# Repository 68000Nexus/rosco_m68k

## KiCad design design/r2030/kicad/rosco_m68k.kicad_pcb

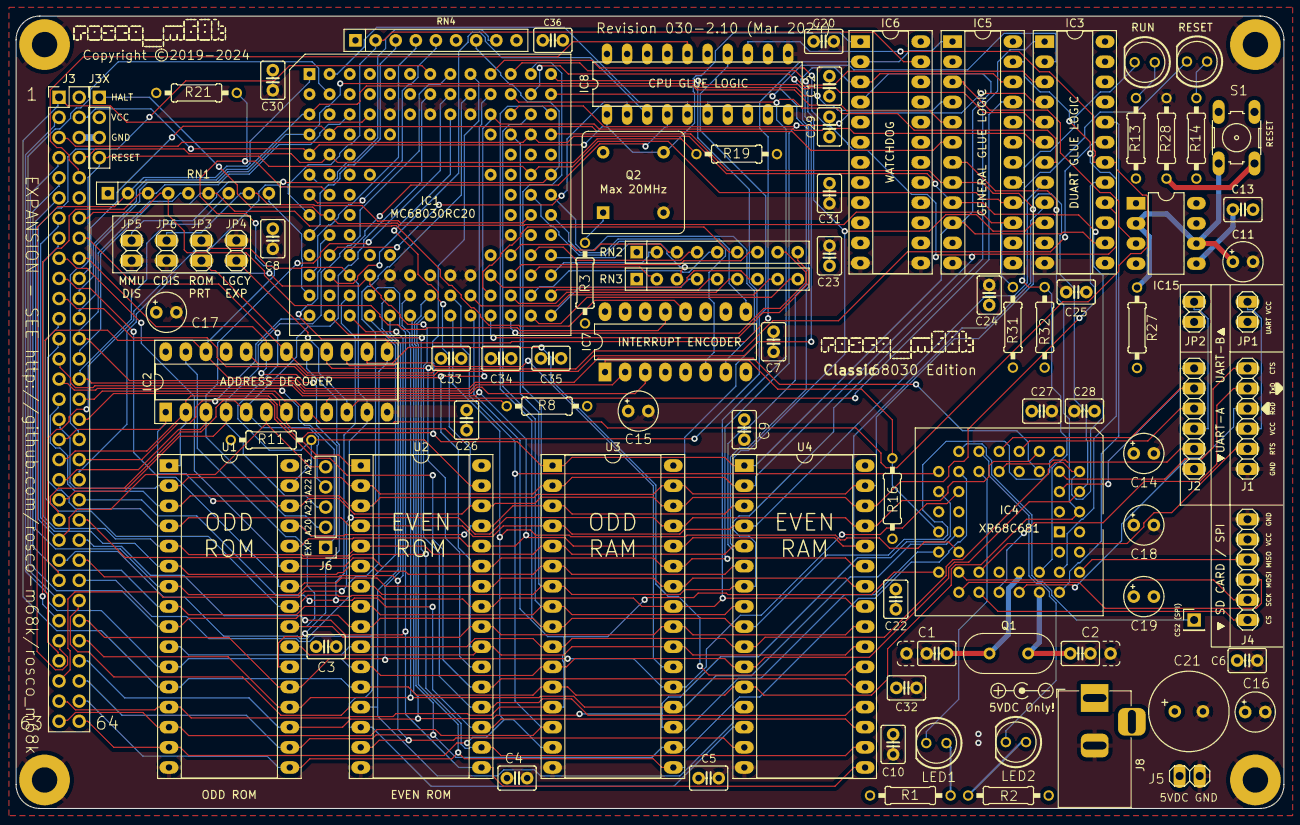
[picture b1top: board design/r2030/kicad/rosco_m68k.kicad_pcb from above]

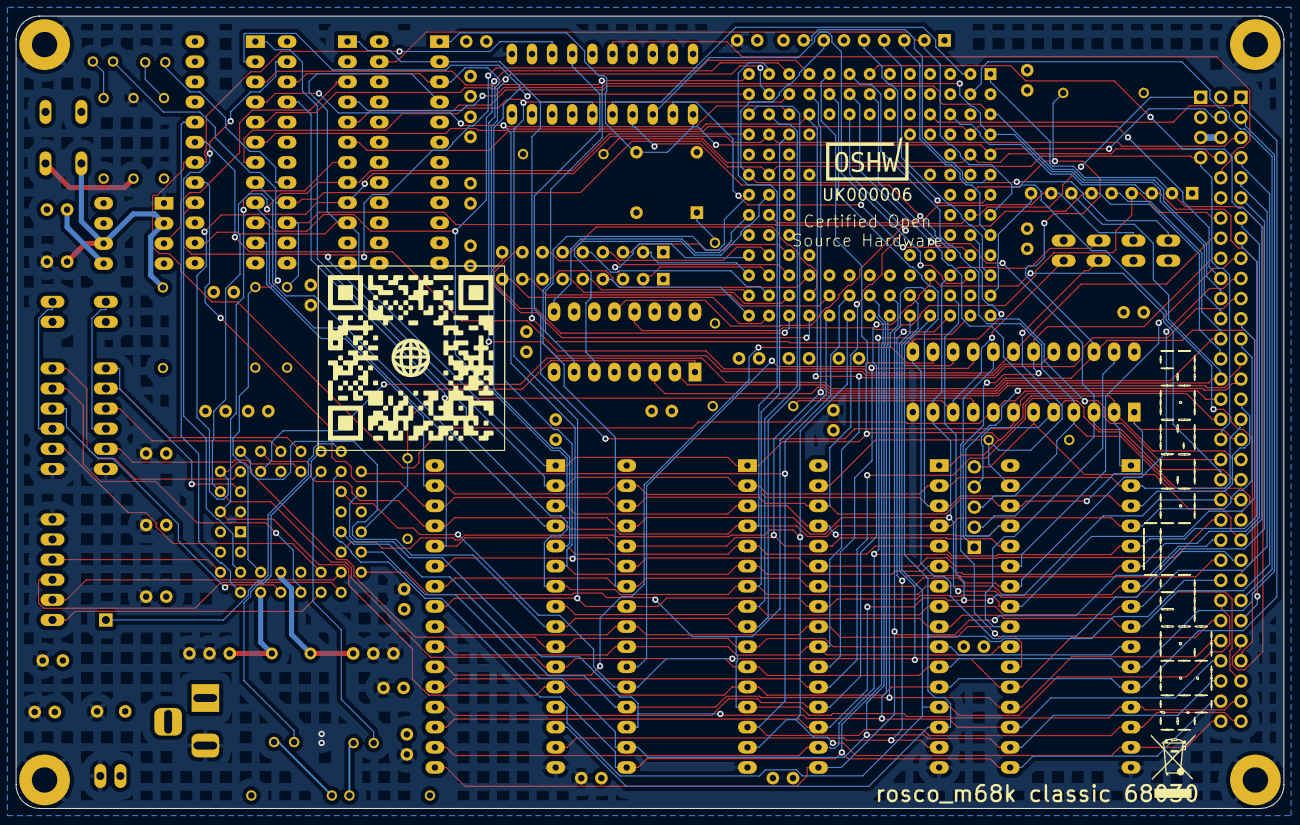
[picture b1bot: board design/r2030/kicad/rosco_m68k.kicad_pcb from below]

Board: 4 copper layers, 160.0 x 100.0 mm, 97 parts (2 on the bottom side), 135 nets.

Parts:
C1, C2: 7pF; C2.5_or_3.5-3
C3, C4, C5, C6, C7, C8, C9, C10, C12, C13, C20, C22, C23, C24, C25, C26, C27, C28, C29, C30, C31, C32, C33, C34, C35, C36: 100nF; C2.5-3
C11, C14, C15, C16, C17, C18, C19: 100uF; E2,5-5
C21: 470uF; E3,5-10
H1, H2, H3, H4: MountingHole; MountingHole_3.2mm_M3_Pad
IC1: MC68030RC_PGA; MC68030RC
IC2, IC3, IC5, IC6: ATF22V10C; DIP-24_W7.62mm_Socket_LongPads
IC4: XR68C681CJTR-F; PLCC-44_THT-Socket
IC7: 74LS148; DIP-16_W7.62mm_LongPads
IC8: ATF16V8BQL; DIL20
IC15: 555N; DIP-8_W7.62mm_LongPads
J1: UART_A; 1X06
J2: UART_B; 1X06
J3: Conn_02x32_Odd_Even; PinHeader_2x32_P2.54mm_Vertical
J3-X1: Conn_01x04_Male; PinHeader_1x04_P2.54mm_Vertical
J4: Conn_01x06; 1X06
J5: PWR; 1X02
J6: Conn_01x05_Male; PinHeader_1x05_P2.54mm_Vertical
J7: Conn_01x01_Male; PinHeader_1x01_P2.54mm_Vertical
J8: Jack-DC; BarrelJack_Horizontal
JP1, JP2, JP3, JP4, JP5, JP6: Jumper; 1X02
LED1, LED3: GREEN; LED5MM
LED2, LED4: RED; LED5MM
OSHW_Mono_0.25_Scale: UK000006; OSHW_Mono_0.25_Scale
Q1: 3.6864MHz; Crystal_HC49-4H_Vertical
Q2: 5H8ET-20.000; Oscillator_DIP-8
R1, R2, R13, R14: 330R; 0207_10
R3, R8, R16, R31, R32: 4K7; 0207_10
R11, R19: 10K; 0207_10
R21: 1K2; 0207_10
R27: 2K2; 0207_10
R28: 270R; 0207_10
RN1, RN4: 4K7; R_Array_SIP9
RN2: 10K; R_Array_SIP9
RN3: R_Network08; R_Array_SIP9
S1: 10-XX; B3F-10XX
U1, U2: SST39SF040; DIP-32_W15.24mm_Socket_LongPads
U3, U4: AS6C4008-55PCN; DIP-32_W15.24mm_Socket_LongPads
rosco_m68k, rosco_m68k_mid: SM-rosco_m68k_logo
weee: WEEE-Logo_5.6x8mm_SilkScreen

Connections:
A0: IC1.A2 (A0), IC8.5 (I4)
A1: IC1.C4 (A1), IC4.2 (A1), IC5.7 (I7), J3.1, U1.12 (A0), U2.12 (A0), U3.12 (A0), U4.12 (A0)
A2: IC1.D13 (A2), IC4.4 (A2), IC5.8 (I8), J3.3, U1.11 (A1), U2.11 (A1), U3.11 (A1), U4.11 (A1)
A3: IC1.D12 (A3), IC4.6 (A3), IC5.9 (I9), J3.5, U1.10 (A2), U2.10 (A2), U3.10 (A2), U4.10 (A2)
A4: IC1.C13 (A4), IC4.7 (A4), J3.7, U1.9 (A3), U2.9 (A3), U3.9 (A3), U4.9 (A3)
A5: IC1.C12 (A5), J3.9, U1.8 (A4), U2.8 (A4), U3.8 (A4), U4.8 (A4)
A6: IC1.D11 (A6), IC3.1 (I1/CLK), J3.11, U1.7 (A5), U2.7 (A5), U3.7 (A5), U4.7 (A5)
A7: IC1.B13 (A7), IC3.2 (I2), J3.13, U1.6 (A6), U2.6 (A6), U3.6 (A6), U4.6 (A6)
A8: IC1.B12 (A8), IC3.3 (I3), J3.15, U1.5 (A7), U2.5 (A7), U3.5 (A7), U4.5 (A7)
A9: IC1.C11 (A9), IC3.4 (I4/PD), J3.17, U1.27 (A8), U2.27 (A8), U3.27 (A8), U4.27 (A8)
A10: IC1.A13 (A10), IC3.5 (I5), J3.19, U1.26 (A9), U2.26 (A9), U3.26 (A9), U4.26 (A9)
A11: IC1.C10 (A11), IC3.6 (I6), J3.21, U1.23 (A10), U2.23 (A10), U3.23 (A10), U4.23 (A10)
A12: IC1.B11 (A12), IC3.7 (I7), J3.23, U1.25 (A11), U2.25 (A11), U3.25 (A11), U4.25 (A11)
A13: IC1.A12 (A13), IC3.8 (I8), J3.25, U1.4 (A12), U2.4 (A12), U3.4 (A12), U4.4 (A12)
A14: IC1.B10 (A14), IC3.9 (I9), J3.27, U1.28 (A13), U2.28 (A13), U3.28 (A13), U4.28 (A13)
A15: IC1.A11 (A15), IC3.10 (I10), J3.29, U1.29 (A14), U2.29 (A14), U3.3 (A14), U4.3 (A14)
A16: IC1.B9 (A16), IC3.11 (I11), J3.31, U1.3 (A15), U2.3 (A15), U3.31 (A15), U4.31 (A15)
A17: IC1.A10 (A17), IC3.16 (IO3), J3.33, U1.2 (A16), U2.2 (A16), U3.2 (A16), U4.2 (A16)
A18: IC1.C8 (A18), IC2.1 (I1/CLK), IC3.17 (I04), J3.35, U1.30 (A17), U2.30 (A17), U3.30 (A17), U4.30 (A17)
A19: IC1.A9 (A19), IC2.2 (I2), IC3.14 (IO1), IC5.10 (I10), IC6.4 (I4/PD), J3.37, U1.1 (A18), U2.1 (A18), U3.1 (A18), U4.1 (A18)
A20: IC1.B8 (A20), IC2.3 (I3), J3.39, J6.2
A21: IC1.A8 (A21), IC2.4 (I4/PD), J3.41, J6.3
A22: IC1.B7 (A22), IC2.5 (I5), J3.43, J6.4
A23: IC1.A7 (A23), IC2.6 (I6), J3.45, J6.5
AS: IC1.J2 (AS), IC2.13 (I13), IC5.1 (I1/CLK), IC6.2 (I2), IC8.6 (I5), J3.47
BERR: IC1.H1 (BERR), IC6.23 (IO10), J3.49, RN4.2 (R1)
BG: IC1.B2 (BG), J3.51
BGACK: IC1.C3 (BGACK), J3.53, RN1.3 (R2)
BOOT: IC2.9 (I9), IC5.21 (IO8)
BR: IC1.A1 (BR), J3.55, RN1.2 (R1)
CBACK: IC1.J1 (CBACK), RN4.3 (R2)
CDIS: IC1.H12 (CDIS), JP6.1 (A), RN1.8 (R7)
CIIN: IC1.L1 (CIIN), RN4.4 (R3)
CLK: IC1.E1 (CLKIN), IC6.1 (I1/CLK), IC8.1 (CLK), J3.4, Q2.5 (OUT)
CPUSP: IC2.20 (IO7), IC5.22 (IO9), IC6.3 (I3)
CTSA: IC4.8 (IP0), J1.6
CTSB: IC4.5 (IP1), J2.6
D0: IC1.N9 (D16), IC4.28 (D0), J3.61, U1.13 (D0), U3.13 (DQ0)
D1: IC1.M8 (D17), IC4.18 (D1), J3.63, U1.14 (D1), U3.14 (DQ1)
D2: IC1.N8 (D18), IC4.27 (D2), J3.64, U1.15 (D2), U3.15 (DQ2)
D3: IC1.N7 (D19), IC4.19 (D3), J3.62, U1.17 (D3), U3.17 (DQ3)
D4: IC1.M7 (D20), IC4.26 (D4), J3.60, U1.18 (D4), U3.18 (DQ4)
D5: IC1.N6 (D21), IC4.20 (D5), J3.58, U1.19 (D5), U3.19 (DQ5)
D6: IC1.M6 (D22), IC4.25 (D6), J3.56, U1.20 (D6), U3.20 (DQ6)
D7: IC1.N5 (D23), IC4.21 (D7), J3.54, U1.21 (D7), U3.21 (DQ7)
D8: IC1.M5 (D24), J3.52, U2.13 (D0), U4.13 (DQ0)
D9: IC1.N4 (D25), J3.50, U2.14 (D1), U4.14 (DQ1)
D10: IC1.N3 (D26), J3.48, U2.15 (D2), U4.15 (DQ2)
D11: IC1.M4 (D27), J3.46, U2.17 (D3), U4.17 (DQ3)
D12: IC1.N2 (D28), J3.44, U2.18 (D4), U4.18 (DQ4)
D13: IC1.M3 (D29), J3.42, U2.19 (D5), U4.19 (DQ5)
D14: IC1.L4 (D30), J3.40, U2.20 (D6), U4.20 (DQ6)
D15: IC1.N1 (D31), J3.38, U2.21 (D7), U4.21 (DQ7)
DBEN: IC1.M1 (DBEN), RN1.9 (R8)
DS: IC1.K2 (DS), IC8.2 (I1)
DSACK0: IC1.F1 (DSACK0), RN4.8 (R7)
DTACK: IC1.G2 (DSACK1), IC2.22 (IO9), IC4.10 (*DTALK), J3.57, R21.2
DUAIACK: IC4.41 (*IACK), IC5.23 (IO10)
DUAIRQ: IC4.24 (INTR), IC7.1 (I4), R16.2
DUASEL: IC3.20 (IO7), IC4.39 (CS)
E: IC8.16 (IO4), J3.10
EVENRAMSEL: IC2.14 (IO1), U4.22 (CE)
EVENROMSEL: IC2.16 (IO3), U2.22 (CE)
EXPSEL: IC2.19 (IO6), J3.18, J6.1
FC0: IC1.D2 (FC0), IC5.6 (I6), J3.20
FC1: IC1.C1 (FC1), IC5.5 (I5), J3.22
FC2: IC1.D1 (FC2), IC5.4 (I4/PD), J3.24
GND: C1.1, C2.1, C3.2, C4.2, C5.2, C6.2, C7.2, C8.2, C9.2, C10.2, C11.-, C12.2, C14.-, C15.-, C16.-, C17.-, C18.-, C19.-, C20.2, C21.-, C22.2, C23.2, C24.2, C25.2, C26.2, C27.2, C28.1, C29.1, C30.1, C31.2, C32.2, C33.2, C34.2, C35.2, C36.2, H1.1, H2.1, H3.1, H4.1, IC1.C5 (GND), IC1.C7 (GND), IC1.C9 (GND), IC1.E3 (GND), IC1.E11 (GND), IC1.F3 (GND), IC1.G3 (GND), IC1.G11 (GND), IC1.J3 (GND), IC1.J11 (GND), IC1.L5 (GND), IC1.L7 (GND), IC1.L8 (GND), IC1.L9 (GND), IC2.12 (GND), IC3.12 (GND), IC4.3 (IP3), IC4.22 (GND), IC4.42 (IP5), IC4.43 (IP4), IC5.12 (GND), IC6.12 (GND), IC6.13 (I13), IC7.5 (EI), IC7.8 (GND), IC7.10 (IO), IC8.10 (GND), IC8.11 (OE), IC15.1 (GND), J1.1, J2.1, J3.6, J3-X1.3, J4.6, J5.2, J8.2, JP4.2 (B), JP5.2 (B), JP6.2 (B), Q2.4 (GND), R28.1, RN2.1 (common), RN3.1 (common), U1.16 (GND), U2.16 (GND), U3.16 (VSS), U4.16 (VSS)
HALT: IC1.H2 (HLT), IC5.15 (IO2), J3-X1.1, R31.1
HWRST: IC5.3 (I3), IC15.3 (Q)
IOSEL: IC2.18 (IO5), IC3.19 (IO6), J3.16
IPL0: IC1.H13 (IPL0), IC7.9 (S0)
IPL1: IC1.G13 (IPL1), IC7.7 (S1)
IPL2: IC1.G12 (IPL2), IC7.6 (S2)
IRQ2: IC7.12 (I2), J3.28, RN1.6 (R5)
IRQ3: IC7.13 (I3), J3.14, RN1.4 (R3)
IRQ5: IC7.2 (I5), J3.26, RN1.5 (R4)
IRQ6: IC7.3 (I6), J3.30, RN1.7 (R6)
LDS: IC2.8 (I8), IC3.18 (IO5), IC8.13 (IO7), J3.32
LGEXP: IC2.10 (I10), JP4.1 (A), R8.2
MMUDIS: IC1.F13 (MMUDIS), JP5.1 (A), RN4.7 (R6)
unnamed: IC4.15 (OP3), LED2.K (C)
unnamed: IC4.16 (OP5), LED1.K (C)
unnamed: C1.2, IC4.36 (X1/CLK), Q1.1
unnamed: C2.2, IC4.37 (X2), Q1.2
unnamed: C13.2, IC15.5 (CV)
unnamed: C11.+, IC15.2 (TR), IC15.6 (THR), R27.1, S1.1 (S)
unnamed: LED1.A, R1.1
unnamed: LED2.A, R2.1
unnamed: LED3.A, R13.1
unnamed: LED4.A, R14.1
unnamed: Q2.1 (EN), R3.2
unnamed: R28.2, S1.3
ODDRAMSEL: IC2.15 (IO2), U3.22 (CE)
ODDROMSEL: IC2.17 (I04), U1.22 (CE)
RESET: IC1.F12 (RESET), IC4.38 (*RESET), IC5.16 (IO3), J3.36, J3-X1.4, LED4.K (C), R32.1
ROM_RW: JP3.2 (B), R11.2, U1.31 (PGM), U2.31 (PGM)
RTSA: IC4.32 (OP0), J1.2
RTSB: IC4.14 (OP1), J2.2
RUNLED: IC5.17 (I04), LED3.K (C)
RW: IC1.L3 (R_W), IC2.11 (I11), IC4.9 (*R/*W), J3.59, JP3.1 (A), U3.29 (WE), U4.29 (WE)
RXDA: IC4.35 (RXDA), J1.4
RXDB: IC4.11 (RXDB), J2.4
SIZ0: IC1.L2 (SIZ0), IC8.3 (I2)
SIZ1: IC1.K3 (SIZ1), IC8.4 (I3)
SPICLK: IC4.30 (OP4), J4.2
SPICS: IC4.31 (OP2), J4.1
SPICS2: IC4.17 (OP7), J7.1
SPIMISO: IC4.40 (IP2), J4.4
SPIMOSI: IC4.29 (OP6), J4.3
STERM: IC1.G1 (STERM), RN4.5 (R4)
TXDA: IC4.33 (TXDA), J1.5
TXDB: IC4.13 (TXDB), J2.5
UD0: IC1.K13 (D0), RN3.3 (R2)
UD1: IC1.K12 (D1), RN2.4 (R3)
UD2: IC1.L13 (D2), RN2.2 (R1)
UD3: IC1.M13 (D3), RN3.5 (R4)
UD4: IC1.L12 (D4), RN3.2 (R1)
UD5: IC1.K11 (D5), RN2.3 (R2)
UD6: IC1.M12 (D6), RN2.5 (R4)
UD7: IC1.L11 (D7), RN2.7 (R6)
UD8: IC1.N13 (D8), RN3.4 (R3)
UD9: IC1.M11 (D9), RN3.6 (R5)
UD10: IC1.L10 (D10), RN3.7 (R6)
UD11: IC1.N12 (D11), RN3.9 (R8)
UD12: IC1.M10 (D12), RN2.6 (R5)
UD13: IC1.N11 (D13), RN2.8 (R7)
UD14: IC1.M9 (D14), RN3.8 (R7)
UD15: IC1.N10 (D15), RN2.9 (R8)
UDS: IC2.7 (I7), IC8.14 (IO6), J3.34
VCC: C3.1, C4.1, C5.1, C6.1, C7.1, C8.1, C9.1, C10.1, C12.1, C13.1, C14.+, C15.+, C16.+, C17.+, C18.+, C19.+, C20.1, C21.+, C22.1, C23.1, C24.1, C25.1, C26.1, C27.1, C28.2, C29.2, C30.2, C31.1, C32.1, C33.1, C34.1, C35.1, C36.1, IC1.C6 (VCC), IC1.D4 (VCC), IC1.D10 (VCC), IC1.F2 (VCC), IC1.F11 (VCC), IC1.H3 (VCC), IC1.H11 (VCC), IC1.K4 (VCC), IC1.K10 (VCC), IC1.L6 (VCC), IC2.24 (VCC), IC3.24 (VCC), IC4.44 (VCC), IC5.24 (VCC), IC6.24 (VCC), IC7.4 (I7), IC7.11 (I1), IC7.16 (VCC), IC8.20 (VCC), IC15.4 (R), IC15.8 (V+), J3.2, J3-X1.2, J4.5, J5.1, J8.1, JP1.2 (B), JP2.2 (B), Q2.8 (Vcc), R1.2, R2.2, R3.1, R8.1, R11.1, R13.2, R14.2, R16.1, R19.1, R21.1, R27.2, R31.2, R32.2, RN1.1 (common), RN4.1 (common), U1.32 (VCC), U2.32 (VCC), U3.32 (VCC), U4.32 (VCC)
VCCUA: J1.3, JP1.1 (A)
VCCUB: J2.3, JP2.1 (A)
VPA: IC1.E2 (AVEC), J3.8, R19.2
WR: IC2.23 (IO10), U1.24 (OE), U2.24 (OE), U3.24 (OE), U4.24 (OE)

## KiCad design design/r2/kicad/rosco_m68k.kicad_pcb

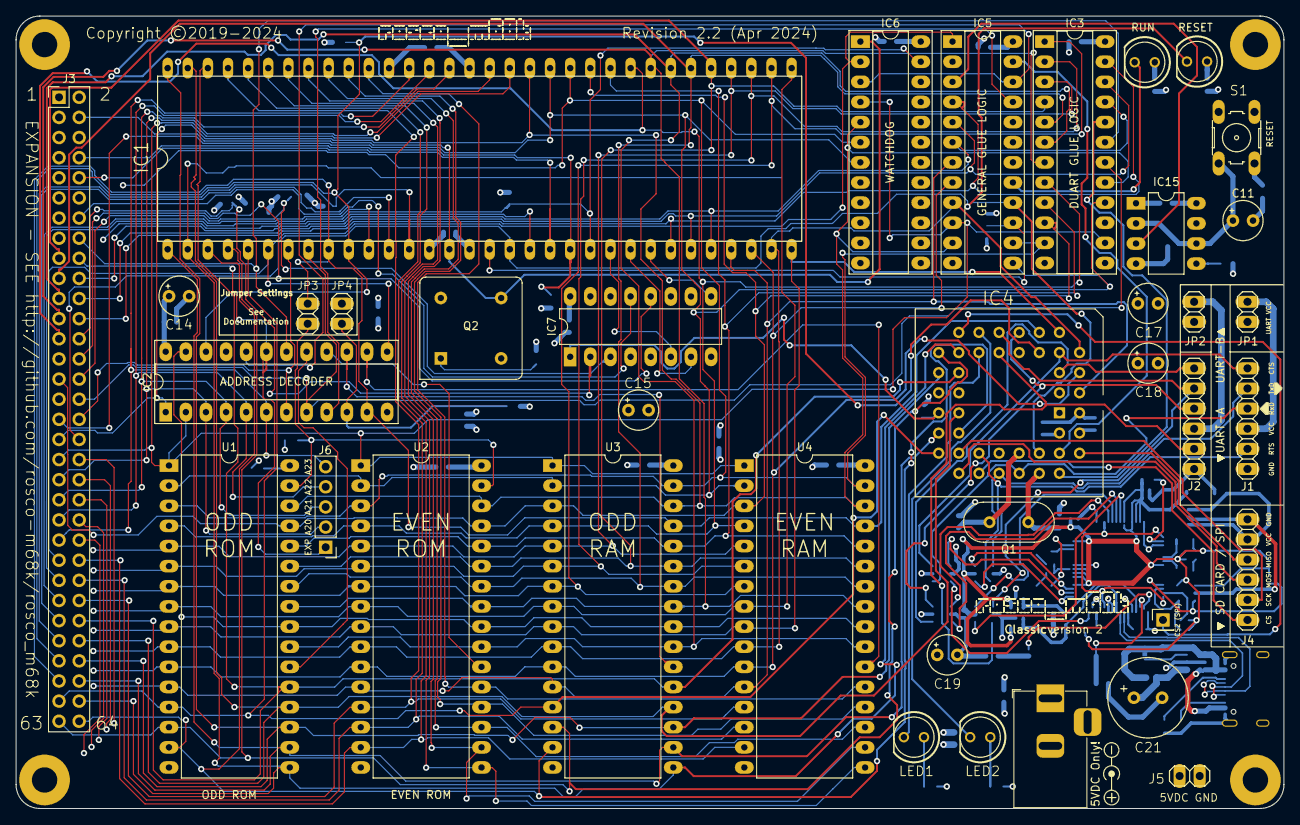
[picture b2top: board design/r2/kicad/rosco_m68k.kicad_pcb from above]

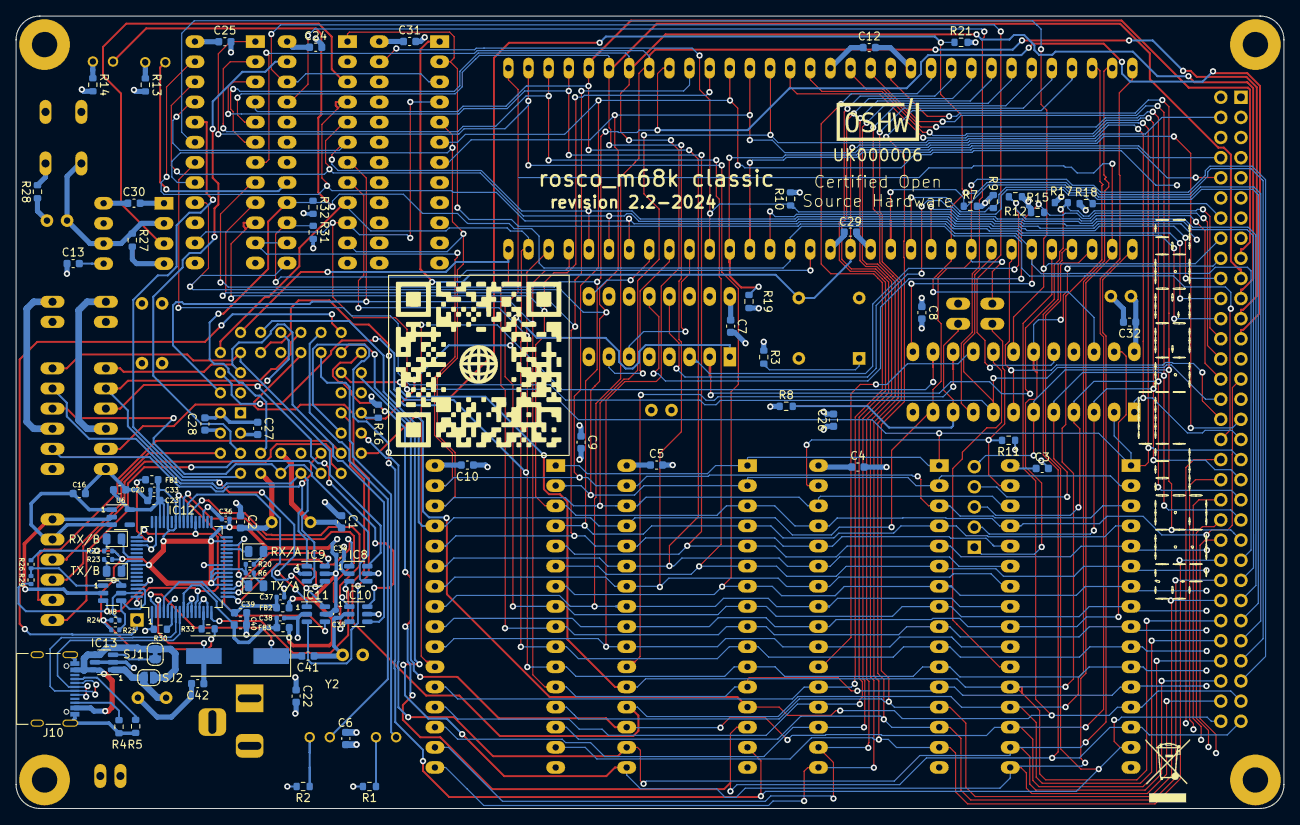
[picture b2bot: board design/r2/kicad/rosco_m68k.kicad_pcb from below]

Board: 4 copper layers, 160.0 x 100.0 mm, 134 parts (90 on the bottom side), 144 nets.

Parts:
BIGROSCO: MD-rosco_m68k_logo
C1, C2: 7pF; C_0603_1608Metric
C3, C4, C5, C6, C7, C8, C9, C10, C12, C13, C22, C24, C25, C26, C27, C28, C29, C30, C31, C32: 100nF; C_0603_1608Metric
C11, C14, C15, C17, C18, C19: 100uF; E2,5-5
C16, C20, C23, C39, C40: 4.7uF; C_0603_1608Metric
C21: 470uF; E3,5-10
C33, C34, C35, C36, C37, C38: 100nF; C_0402_1005Metric
C41, C42: 27pF; C_0603_1608Metric
FB1, FB2, FB3: BLM18HE152SN1D; L_0603_1608Metric
H1, H2, H3, H4: MountingHole; MountingHole_3.2mm_M3_Pad
IC1: MC68010P10; DIL64
IC2, IC3, IC5, IC6: ATF22V10C; DIP-24_W7.62mm_Socket_LongPads
IC4: XR68C681CJTR-F; PLCC-44_THT-Socket
IC7: 74LS148; DIP-16_W7.62mm_LongPads
IC8, IC9, IC10, IC11: SN74LVC2G17; SOT-23-6
IC12: FT2232HL; LQFP-64_10x10mm_P0.5mm
IC13: TPS22929D; SOT-23-6
IC15: 555N; DIP-8_W7.62mm_LongPads
J1: UART_A; 1X06
J2: UART_B; 1X06
J3: Conn_02x32_Odd_Even; PinHeader_2x32_P2.54mm_Vertical
J4: Conn_01x06; 1X06
J5: PWR; 1X02
J6: Conn_01x05_Male; PinHeader_1x05_P2.54mm_Vertical
J7: Conn_01x01_Male; PinHeader_1x01_P2.54mm_Vertical
J9: Jack-DC; BarrelJack_Horizontal
J10: USB_C_Receptacle_PowerOnly_6P; USB_C_Receptacle_Palconn_UTC16-G
JP1, JP2, JP3, JP4: Jumper; 1X02
LED1, LED3: GREEN; LED5MM
LED2, LED4: RED; LED5MM
LED5, LED6, LED7, LED8: RED; LED_0805_2012Metric
OSHW_Mono_0.25_Scale: UK000006; OSHW_Mono_0.25_Scale
POLARITY: Symbol_Barrel_Polarity
Q1: 3.6864MHz; Crystal_HC49-4H_Vertical
Q2: 5H8ET-10.000; Oscillator_DIP-8
R1, R2, R13, R14, R33: 1K; R_0603_1608Metric
R3, R7, R8, R9, R10, R12, R15, R16, R17, R18, R31, R32: 4K7; R_0603_1608Metric
R4, R5: 5.1K; R_0603_1608Metric
R6, R20, R22, R23: 2K; R_0402_1005Metric
R11, R19: 10K; R_0603_1608Metric
R21: 1K2; R_0603_1608Metric
R24, R25, R26: 10K; R_0402_1005Metric
R27: 2K2; R_0603_1608Metric
R28: 270R; R_0603_1608Metric
R29: 2.2K; R_0402_1005Metric
R30: 12K; R_0603_1608Metric
S1: 10-XX; B3F-10XX
SJ1: SHORT; SolderJumper-2_P1.3mm_Bridged_RoundedPad1.0x1.5mm
SJ2: OPEN; SolderJumper-2_P1.3mm_Open_RoundedPad1.0x1.5mm
U1, U2: SST39SF040; DIP-32_W15.24mm_LongPads
U3, U4: AS6C4008-55PCN; DIP-32_W15.24mm_LongPads
U6: AP2127K-3.3; SOT-23-5
U8: 93LC56BT-I/OT; SOT-23-6
WEEE: WEEE-Logo_5.6x8mm_SilkScreen
Y2: 12MHz; Crystal_SMD_HC49-SD
rosco: SM-rosco_m68k_logo

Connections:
+3V3: C20.1, C23.1, C33.1, C34.1, C35.1, C36.1, FB1.2, FB2.2, FB3.2, IC9.5 (VCC), IC11.5 (VCC), IC12.20 (VCCIO), IC12.22 (ADBUS5), IC12.23 (ADBUS6), IC12.24 (ADBUS7), IC12.31 (VCCIO), IC12.42 (VCCIO), IC12.44 (BDBUS5), IC12.45 (BDBUS6), IC12.46 (BDBUS7), IC12.56 (VCCIO), R6.2, R20.2, R22.2, R23.2, R24.1, R25.2, R26.2, R33.2, U6.5 (VOUT), U8.6 (VCC)
/FTDI (Optional)/EE_CLK: IC12.62 (EECLK), R25.1, U8.4 (CLK)
/FTDI (Optional)/EE_CS: IC12.63 (EECS), R24.2, U8.5 (CS)
/FTDI (Optional)/EE_DAT: IC12.61 (EEDATA), R29.1, U8.3 (DI)
/FTDI (Optional)/FTDI_CTSA: IC9.6 (Y1), IC12.19 (ADBUS3)
/FTDI (Optional)/FTDI_CTSB: IC11.4 (Y2), IC12.41 (BDBUS3)
/FTDI (Optional)/FTDI_RTSA: IC8.1 (IN_A), IC12.18 (ADBUS2)
/FTDI (Optional)/FTDI_RTSB: IC10.3 (IN_B), IC12.40 (BDBUS2)
/FTDI (Optional)/FTDI_RXA: IC9.4 (Y2), IC12.17 (ADBUS1)
/FTDI (Optional)/FTDI_RXB: IC11.6 (Y1), IC12.39 (BDBUS1)
/FTDI (Optional)/FTDI_TXA: IC8.3 (IN_B), IC12.16 (ADBUS0)
/FTDI (Optional)/FTDI_TXB: IC10.1 (IN_A), IC12.38 (BDBUS0)
/FTDI (Optional)/VCORE: IC12.12 (VCORE), IC12.37 (VCORE), IC12.49 (VREGOUT), IC12.64 (VCORE)
/FTDI (Optional)/VPHY: C37.1, C39.1, FB2.1, IC12.4 (VPHY)
/FTDI (Optional)/VPLL: C38.1, C40.1, FB3.1, IC12.9 (VPLL)
A1: IC1.29 (A1), IC4.2 (A1), IC5.7 (I7), J3.1, U1.12 (A0), U2.12 (A0), U3.12 (A0), U4.12 (A0)
A2: IC1.30 (A2), IC4.4 (A2), IC5.8 (I8), J3.3, U1.11 (A1), U2.11 (A1), U3.11 (A1), U4.11 (A1)
A3: IC1.31 (A3), IC4.6 (A3), IC5.9 (I9), J3.5, U1.10 (A2), U2.10 (A2), U3.10 (A2), U4.10 (A2)
A4: IC1.32 (A4), IC4.7 (A4), J3.7, U1.9 (A3), U2.9 (A3), U3.9 (A3), U4.9 (A3)
A5: IC1.33 (A5), J3.9, U1.8 (A4), U2.8 (A4), U3.8 (A4), U4.8 (A4)
A6: IC1.34 (A6), IC3.1 (I1/CLK), J3.11, U1.7 (A5), U2.7 (A5), U3.7 (A5), U4.7 (A5)
A7: IC1.35 (A7), IC3.2 (I2), J3.13, U1.6 (A6), U2.6 (A6), U3.6 (A6), U4.6 (A6)
A8: IC1.36 (A8), IC3.3 (I3), J3.15, U1.5 (A7), U2.5 (A7), U3.5 (A7), U4.5 (A7)
A9: IC1.37 (A9), IC3.4 (I4/PD), J3.17, U1.27 (A8), U2.27 (A8), U3.27 (A8), U4.27 (A8)
A10: IC1.38 (A10), IC3.5 (I5), J3.19, U1.26 (A9), U2.26 (A9), U3.26 (A9), U4.26 (A9)
A11: IC1.39 (A11), IC3.6 (I6), J3.21, U1.23 (A10), U2.23 (A10), U3.23 (A10), U4.23 (A10)
A12: IC1.40 (A12), IC3.7 (I7), J3.23, U1.25 (A11), U2.25 (A11), U3.25 (A11), U4.25 (A11)
A13: IC1.41 (A13), IC3.8 (I8), J3.25, U1.4 (A12), U2.4 (A12), U3.4 (A12), U4.4 (A12)
A14: IC1.42 (A14), IC3.9 (I9), J3.27, U1.28 (A13), U2.28 (A13), U3.28 (A13), U4.28 (A13)
A15: IC1.43 (A15), IC3.10 (I10), J3.29, U1.29 (A14), U2.29 (A14), U3.3 (A14), U4.3 (A14)
A16: IC1.44 (A16), IC3.11 (I11), IC5.14 (IO1), IC6.6 (I6), J3.31, U1.3 (A15), U2.3 (A15), U3.31 (A15), U4.31 (A15)
A17: IC1.45 (A17), IC3.16 (IO3), IC5.13 (I13), IC6.7 (I7), J3.33, U1.2 (A16), U2.2 (A16), U3.2 (A16), U4.2 (A16)
A18: IC1.46 (A18), IC2.1 (I1/CLK), IC3.17 (I04), IC5.11 (I11), IC6.5 (I5), J3.35, U1.30 (A17), U2.30 (A17), U3.30 (A17), U4.30 (A17)
A19: IC1.47 (A19), IC2.2 (I2), IC3.14 (IO1), IC5.10 (I10), IC6.4 (I4/PD), J3.37, U1.1 (A18), U2.1 (A18), U3.1 (A18), U4.1 (A18)
A20: IC1.48 (A20), IC2.3 (I3), J3.39, J6.2
A21: IC1.50 (A21), IC2.4 (I4/PD), J3.41, J6.3
A22: IC1.51 (A22), IC2.5 (I5), J3.43, J6.4
A23: IC1.52 (A23), IC2.6 (I6), J3.45, J6.5
AS: IC1.6 (AS), IC2.13 (I13), IC5.1 (I1/CLK), IC6.2 (I2), J3.47
BERR: IC1.22 (BERR), IC6.23 (IO10), J3.49, R10.1
BG: IC1.11 (BG), J3.51
BGACK: IC1.12 (BGACK), J3.53, R9.1
BOOT: IC2.9 (I9), IC5.21 (IO8)
BR: IC1.13 (BR), J3.55, R7.1
CLK: IC1.15 (CLK), IC6.1 (I1/CLK), J3.4, Q2.5 (OUT)
CPUSP: IC2.20 (IO7), IC5.22 (IO9), IC6.3 (I3)
CTSA: IC4.8 (IP0), IC8.6 (Y1), J1.6
CTSB: IC4.5 (IP1), IC10.4 (Y2), J2.6
D0: IC1.5 (D0), IC4.28 (D0), J3.61, U1.13 (D0), U3.13 (DQ0)
D1: IC1.4 (D1), IC4.18 (D1), J3.63, U1.14 (D1), U3.14 (DQ1)
D2: IC1.3 (D2), IC4.27 (D2), J3.64, U1.15 (D2), U3.15 (DQ2)
D3: IC1.2 (D3), IC4.19 (D3), J3.62, U1.17 (D3), U3.17 (DQ3)
D4: IC1.1 (D4), IC4.26 (D4), J3.60, U1.18 (D4), U3.18 (DQ4)
D5: IC1.64 (D5), IC4.20 (D5), J3.58, U1.19 (D5), U3.19 (DQ5)
D6: IC1.63 (D6), IC4.25 (D6), J3.56, U1.20 (D6), U3.20 (DQ6)
D7: IC1.62 (D7), IC4.21 (D7), J3.54, U1.21 (D7), U3.21 (DQ7)
D8: IC1.61 (D8), J3.52, U2.13 (D0), U4.13 (DQ0)
D9: IC1.60 (D9), J3.50, U2.14 (D1), U4.14 (DQ1)
D10: IC1.59 (D10), J3.48, U2.15 (D2), U4.15 (DQ2)
D11: IC1.58 (D11), J3.46, U2.17 (D3), U4.17 (DQ3)
D12: IC1.57 (D12), J3.44, U2.18 (D4), U4.18 (DQ4)
D13: IC1.56 (D13), J3.42, U2.19 (D5), U4.19 (DQ5)
D14: IC1.55 (D14), J3.40, U2.20 (D6), U4.20 (DQ6)
D15: IC1.54 (D15), J3.38, U2.21 (D7), U4.21 (DQ7)
DTACK: IC1.10 (DTACK), IC2.22 (IO9), IC4.10 (*DTALK), J3.57, R21.2
DUAIACK: IC4.41 (*IACK), IC5.23 (IO10)
DUAIRQ: IC4.24 (INTR), IC7.1 (I4), R16.2
DUASEL: IC3.20 (IO7), IC4.39 (CS)
E: IC1.20 (E), J3.10
EVENRAMSEL: IC2.14 (IO1), U4.22 (CE)
EVENROMSEL: IC2.16 (IO3), U2.22 (CE)
EXPSEL: IC2.19 (IO6), J3.18, J6.1
FC0: IC1.28 (FC0), IC3.21 (IO8), IC5.6 (I6), J3.20
FC1: IC1.27 (FC1), IC3.22 (IO9), IC5.5 (I5), J3.22
FC2: IC1.26 (FC2), IC3.23 (IO10), IC5.4 (I4/PD), J3.24
GND: C1.1, C2.1, C3.2, C4.2, C5.2, C6.2, C7.2, C8.2, C9.2, C10.2, C11.-, C12.2, C14.-, C15.-, C16.2, C17.-, C18.-, C19.-, C20.2, C21.-, C22.2, C23.2, C24.2, C25.2, C26.2, C27.2, C28.2, C29.2, C30.2, C31.2, C32.2, C33.2, C34.2, C35.2, C36.2, C37.2, C38.2, C39.2, C40.2, C41.1, C42.1, H1.1, H2.1, H3.1, H4.1, IC1.16 (GND@1), IC1.53 (GND@2), IC2.12 (GND), IC3.12 (GND), IC4.3 (IP3), IC4.22 (GND), IC4.42 (IP5), IC4.43 (IP4), IC5.12 (GND), IC6.12 (GND), IC6.13 (I13), IC7.5 (EI), IC7.8 (GND), IC7.10 (IO), IC8.2 (GND), IC9.2 (GND), IC10.2 (GND), IC11.2 (GND), IC12.1 (GND), IC12.5 (GND), IC12.10 (AGND), IC12.11 (GND), IC12.13 (TEST), IC12.15 (GND), IC12.25 (GND), IC12.35 (GND), IC12.47 (GND), IC12.51 (GND), IC13.2 (GND), IC13.5 (GND), IC15.1 (GND), J1.1, J2.1, J3.6, J4.6, J5.2, J9.2, J10.A1 (GND), J10.A12 (GND), J10.B1 (GND), J10.B12 (GND), J10.S1 (SHIELD), JP4.2 (B), Q2.4 (GND), R4.2, R5.1, R28.1, R30.1, U1.16 (GND), U2.16 (GND), U3.16 (VSS), U4.16 (VSS), U6.2 (GND), U8.2 (GND)
HALT: IC1.17 (HALT), IC5.15 (IO2), R31.1
HWRST: IC5.3 (I3), IC15.3 (Q)
IOSEL: IC2.18 (IO5), IC3.19 (IO6), J3.16
IPL0: IC1.25 (IPL0), IC7.9 (S0)
IPL1: IC1.24 (IPL1), IC7.7 (S1)
IPL2: IC1.23 (IPL2), IC7.6 (S2)
IRQ2: IC7.12 (I2), J3.28, R15.2
IRQ3: IC7.13 (I3), J3.14, R18.2
IRQ5: IC7.2 (I5), J3.26, R17.2
IRQ6: IC7.3 (I6), J3.30, R12.2
LDS: IC1.8 (LDS), IC2.8 (I8), IC3.18 (IO5), J3.32
LGEXP: IC2.10 (I10), JP4.1 (A), R8.2
unnamed: IC4.15 (OP3), LED2.K (C)
unnamed: IC4.16 (OP5), LED1.K (C)
unnamed: C1.2, IC4.36 (X1/CLK), Q1.1
unnamed: C2.2, IC4.37 (X2), Q1.2
unnamed: IC12.29 (ACBUS3), LED5.1 (K)
unnamed: IC12.30 (ACBUS4), LED6.1 (K)
unnamed: IC12.54 (BCBUS3), LED7.1 (K)
unnamed: IC12.55 (BCBUS4), LED8.1 (K)
unnamed: C41.2, IC12.2 (OSCI), Y2.1
unnamed: C42.2, IC12.3 (OSCO), Y2.2
unnamed: IC12.6 (REF), R30.2
unnamed: FB1.1, IC12.50 (VREGIN)
unnamed: IC12.14 (~RESET), R33.1
unnamed: IC13.3 (ON), SJ1.2
unnamed: IC13.4 (VIN), IC13.6 (VIN), J10.A4 (VBUS), J10.A9 (VBUS), J10.B4 (VBUS), J10.B9 (VBUS), SJ1.1, SJ2.1
unnamed: C13.2, IC15.5 (CV)
unnamed: C11.+, IC15.2 (TR), IC15.6 (THR), R27.1, S1.1 (S)
unnamed: J10.A5 (CC1), R5.2
unnamed: J10.B5 (CC2), R4.1
unnamed: LED1.A, R1.1
unnamed: LED2.A, R2.1
unnamed: LED3.A, R13.1
unnamed: LED4.A, R14.1
unnamed: LED5.2 (A), R6.1
unnamed: LED6.2 (A), R20.1
unnamed: LED7.2 (A), R22.1
unnamed: LED8.2 (A), R23.1
unnamed: Q2.1 (EN), R3.2
unnamed: R28.2, S1.3
unnamed: R26.1, R29.2, U8.1 (DO)
ODDRAMSEL: IC2.15 (IO2), U3.22 (CE)
ODDROMSEL: IC2.17 (I04), U1.22 (CE)
RESET: IC1.18 (RESET), IC4.38 (*RESET), IC5.16 (IO3), J3.36, LED4.K (C), R32.1
ROM_RW: JP3.2 (B), R11.2, U1.31 (PGM), U2.31 (PGM)
RTSA: IC4.32 (OP0), IC9.1 (IN_A), J1.2
RTSB: IC4.14 (OP1), IC11.3 (IN_B), J2.2
RUNLED: IC5.17 (I04), LED3.K (C)
RW: IC1.9 (R/W), IC2.11 (I11), IC4.9 (*R/*W), J3.59, JP3.1 (A), U3.29 (WE), U4.29 (WE)
RXDA: IC4.35 (RXDA), IC8.4 (Y2), J1.4
RXDB: IC4.11 (RXDB), IC10.6 (Y1), J2.4
SPICLK: IC4.30 (OP4), J4.2
SPICS: IC4.31 (OP2), J4.1
SPICS2: IC4.17 (OP7), J7.1
SPIMISO: IC4.40 (IP2), J4.4
SPIMOSI: IC4.29 (OP6), J4.3
TXDA: IC4.33 (TXDA), IC9.3 (IN_B), J1.5
TXDB: IC4.13 (TXDB), IC11.1 (IN_A), J2.5
UDS: IC1.7 (UDS), IC2.7 (I7), J3.34
USB_DN: IC12.7 (DM), J10.A7 (D-), J10.B7 (D-)
USB_DP: IC12.8 (DP), J10.A6 (D+), J10.B6 (D+)
VCC: C3.1, C4.1, C5.1, C6.1, C7.1, C8.1, C9.1, C10.1, C12.1, C13.1, C14.+, C15.+, C16.1, C17.+, C18.+, C19.+, C21.+, C22.1, C24.1, C25.1, C26.1, C27.1, C28.1, C29.1, C30.1, C31.1, C32.1, IC1.14 (VCC@1), IC1.49 (VCC@2), IC2.24 (VCC), IC3.24 (VCC), IC4.44 (VCC), IC5.24 (VCC), IC6.24 (VCC), IC7.4 (I7), IC7.11 (I1), IC7.16 (VCC), IC8.5 (VCC), IC10.5 (VCC), IC13.1 (VOUT), IC15.4 (R), IC15.8 (V+), J3.2, J4.5, J5.1, J9.1, JP1.2 (B), JP2.2 (B), Q2.8 (Vcc), R1.2, R2.2, R3.1, R7.2, R8.1, R9.2, R10.2, R11.1, R12.1, R13.2, R14.2, R15.1, R16.1, R17.1, R18.1, R19.1, R21.1, R27.2, R31.2, R32.2, SJ2.2, U1.32 (VCC), U2.32 (VCC), U3.32 (VCC), U4.32 (VCC), U6.1 (VIN), U6.3 (EN)
VCCUA: J1.3, JP1.1 (A)
VCCUB: J2.3, JP2.1 (A)
VMA: IC1.19 (VMA), J3.12
VPA: IC1.21 (VPA), J3.8, R19.2
WR: IC2.23 (IO10), U1.24 (OE), U2.24 (OE), U3.24 (OE), U4.24 (OE)

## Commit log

2024-03-29 Add initial file test
2024-03-30 Updated for latest toolchain
2024-04-01 Initial newlib tests
2024-04-01 Remove old test

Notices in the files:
design/r2/kicad/rosco_m68k.kicad_pcb:
Open Source Hardware licenced under CERN Open Hardware Licence
Copyright ©2019-2024 Ross Bamford & Contributors
